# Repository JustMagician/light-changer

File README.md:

# light_changer

A brand new atopile project!

Created by Pepper Powderly <pepper@atopile.io>

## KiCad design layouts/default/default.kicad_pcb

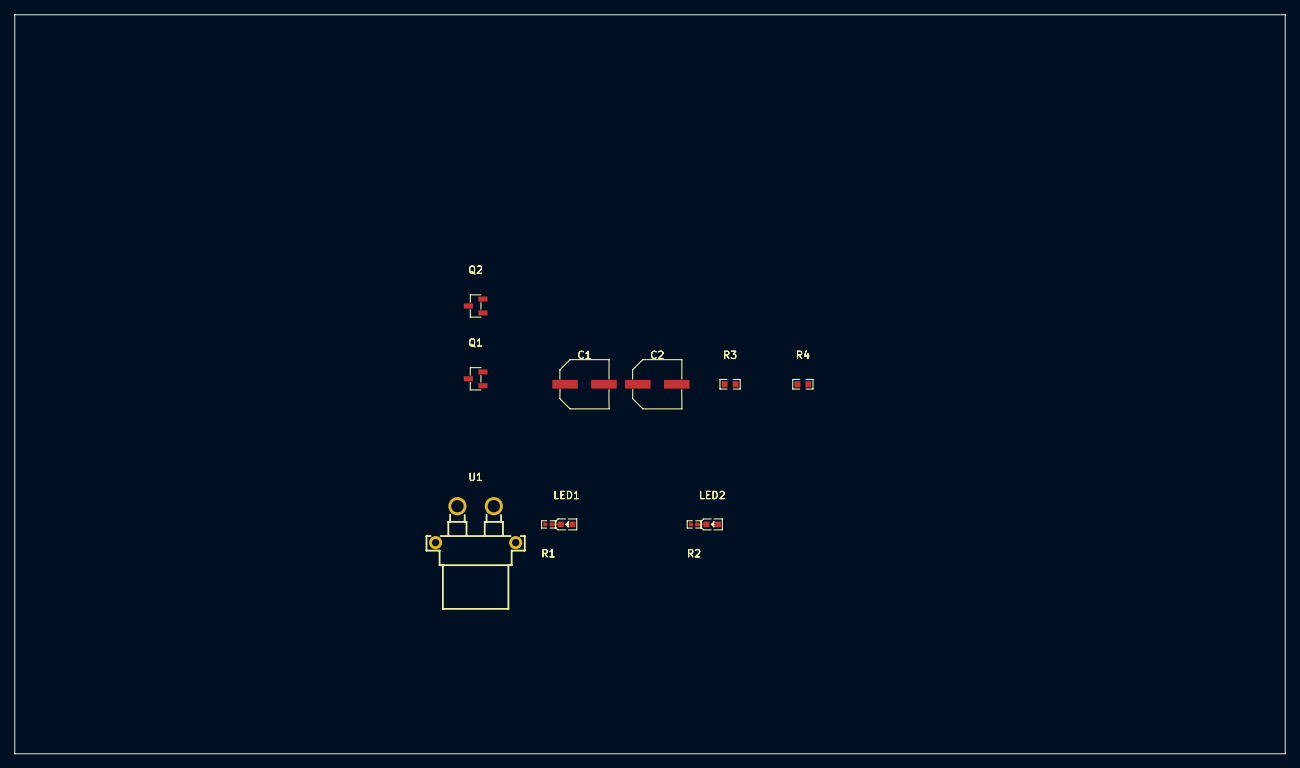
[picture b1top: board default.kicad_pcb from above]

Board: 2 copper layers, 174.5 x 101.5 mm, 11 parts (0 on the bottom side), 8 nets.

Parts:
C1, C2: CAP-SMD_BD6.3-L6.6-W6.6-FD
LED1, LED2: LED0603-RD
Q1, Q2: SOT-23-3_L2.9-W1.3-P1.90-LS2.4-BR
R1, R2: 10kΩ ±1% 62.5mW; R0402
R3: 100kΩ ±1% 100mW; R0603
R4: 10kΩ ±1% 100mW; R0603
U1: CONN-TH_XT30PW-F-1

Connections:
GND_PAD: Q1.2, Q2.2, U1.2
VIN_PAD: LED1.2, LED2.2, R3.1, R4.1, U1.1
footprint-cathode-0: LED1.1, R1.1
footprint-cathode-1: LED2.1, R2.1
led1.low: C1.1, Q1.3, R1.2
led2.low: C2.1, Q2.3, R2.2
r1.cathode: C1.2, Q2.1, R3.2
r2.cathode: C2.2, Q1.1, R4.2

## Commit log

2025-09-28 init
2025-09-28 Changes n stuff
2025-09-29 Wild stuff
2025-09-29 sdfadsf
2025-09-29 messy
2025-09-29 progreesa
